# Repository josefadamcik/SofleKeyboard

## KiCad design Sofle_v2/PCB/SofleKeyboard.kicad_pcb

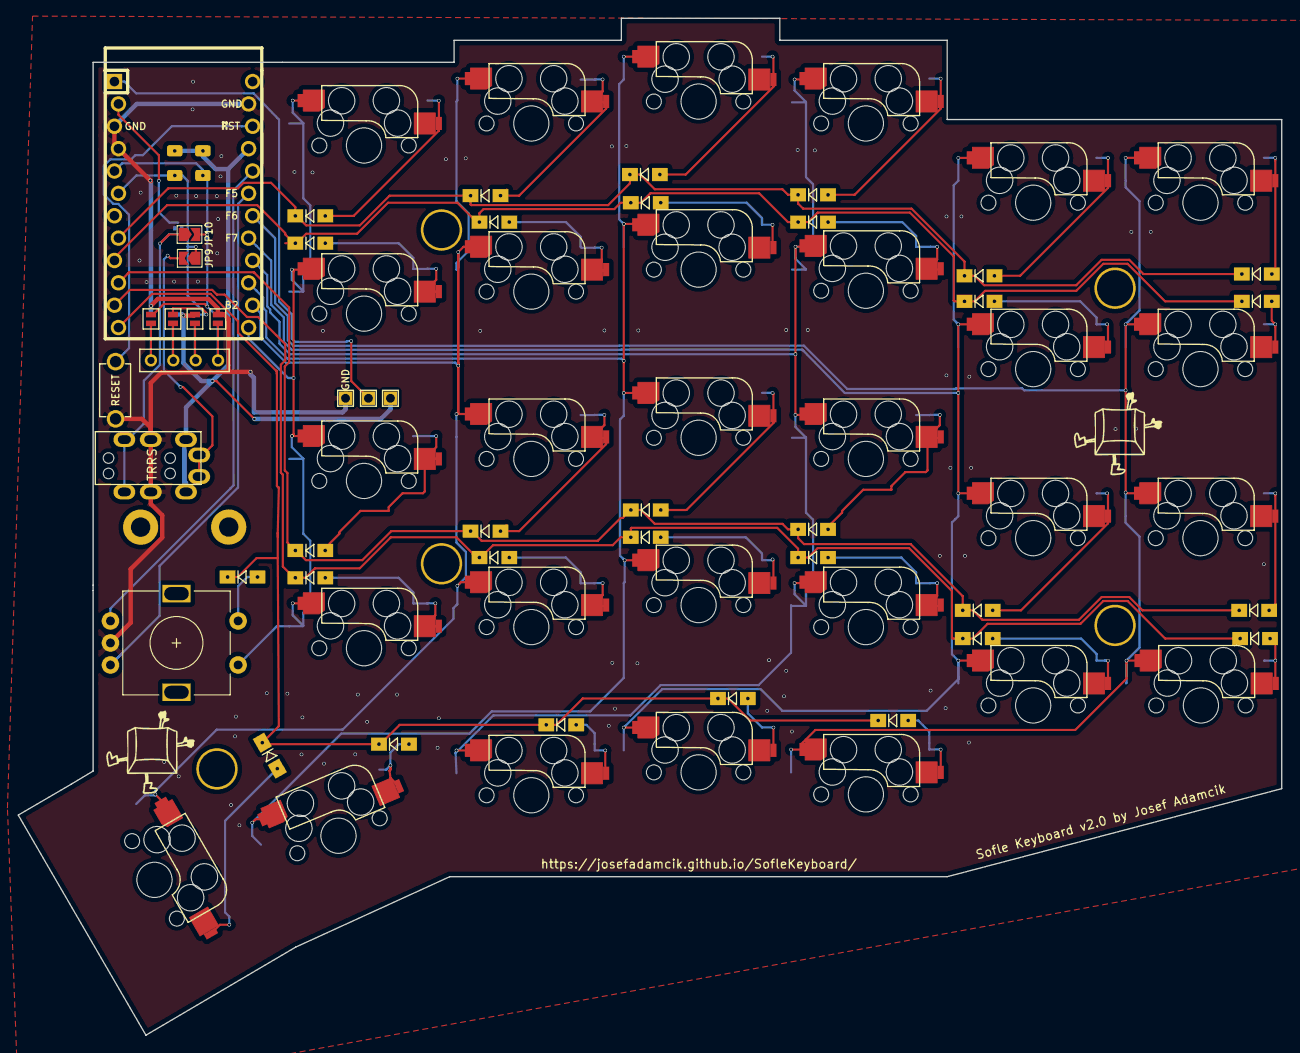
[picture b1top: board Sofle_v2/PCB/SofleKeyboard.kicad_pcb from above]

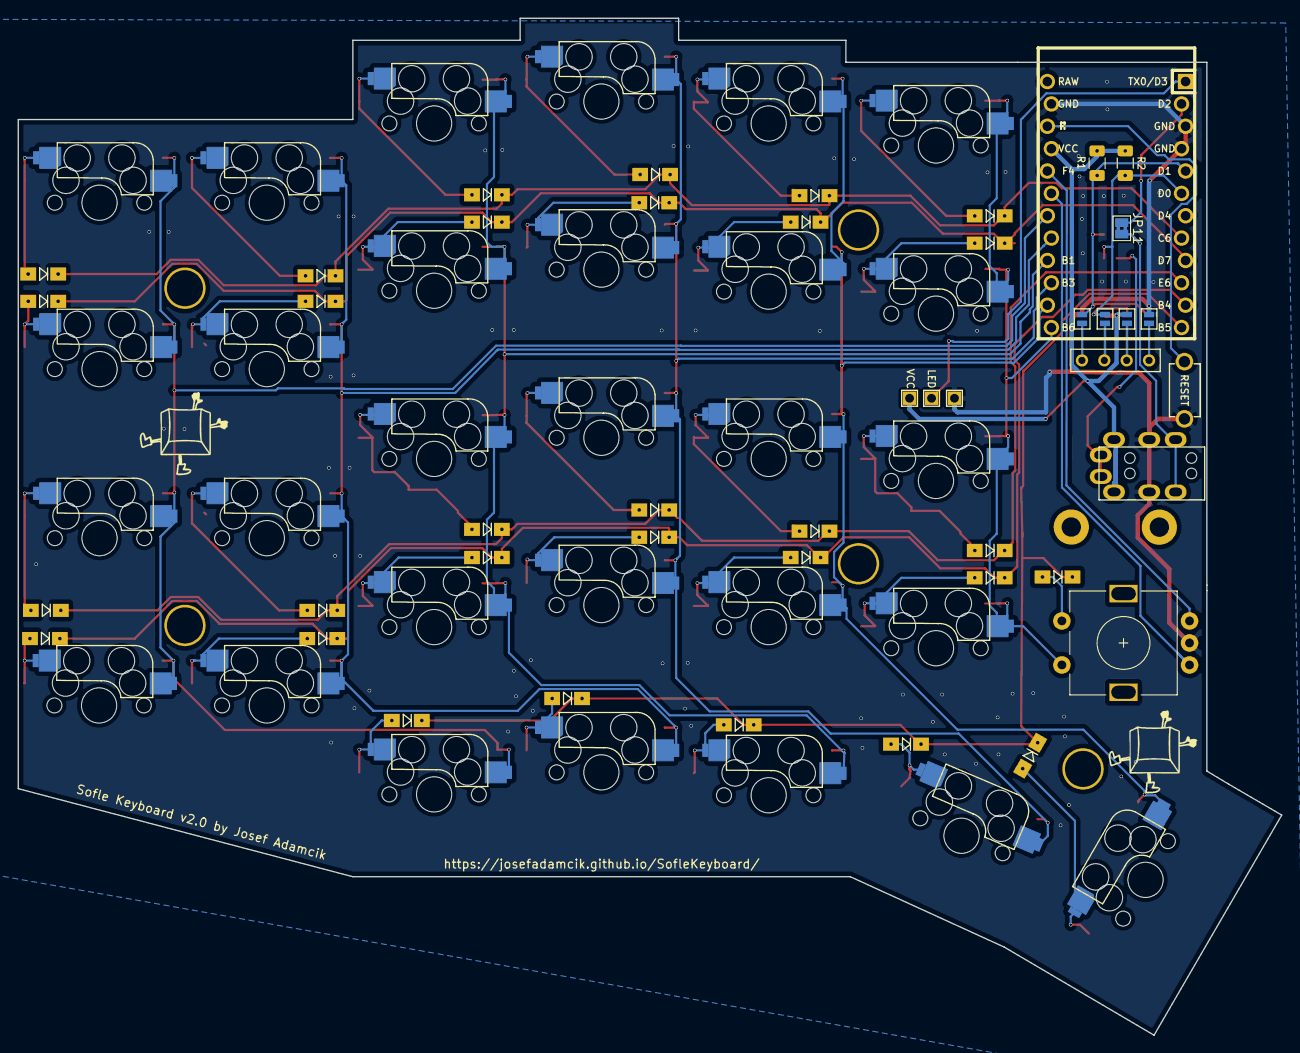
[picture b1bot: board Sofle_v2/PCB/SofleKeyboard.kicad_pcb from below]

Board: 2 copper layers, 143.5 x 115.5 mm, 89 parts (9 on the bottom side), 56 nets.

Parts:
D1, D2, D3, D4, D5, D6, D7, D8, D9, D10, D11, D12, D13, D14, D15, D16, D17, D18, D19, D20, D21, D22, D23, D24, D25, D26, D27, D28, D29, D30: D; Diode_SOD123
J1: LED
J2: 4PIN; MJ-4PP-9
J3: OLED; OLED_4Pin
JP1, JP2, JP3, JP4, JP5, JP6, JP7, JP8: Jumper_NO_Small; Jumper
JP9: I2CSCL; SolderJumper-2_P1.3mm_Open_TrianglePad1.0x1.5mm
JP10: IC2SDA; SolderJumper-2_P1.3mm_Open_TrianglePad1.0x1.5mm
JP11: Serial; SolderJumper-2_P1.3mm_Bridged2Bar_Pad1.0x1.5mm
R1, R2: R; R_1206_DoubleSided
RSW1: SW_RST; TACT_SWITCH_TVBP06
Ref**: Val**; SofleLogoSmall
Ref**#2, Ref**#3, Ref**#4: Val**; SofleLogoSmall
SW1, SW2, SW3, SW4, SW5, SW6, SW7, SW8, SW9, SW10, SW11, SW12, SW13, SW14, SW15, SW16, SW17, SW18, SW19, SW20, SW21, SW22, SW23, SW24, SW27, SW28, SW29, SW30: SW_PUSH; CherryMX_Hotswap
SW25: Rotary_Encoder_Switch; RotaryEncoder_Alps_EC11E-Switch_Vertical_H20mm-keebio_modif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
SW26: SW_PUSH; CherryMX_Hotswap_1.5
TH1, TH2: HOLE; M2_HOLE_PCB
TH3, TH4, TH5, TH6, TH7: HOLE; HOLE_M2_TH
U1: ProMicro; ArduinoProMicro-ZigZag-DoubleSided

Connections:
/i2c_c: J2.4, JP9.2
/i2c_d: J2.3, JP10.1, JP11.2
DATA: JP11.1, U1.2
ENCA: SW25.A, U1.20
ENCB: SW25.B, U1.19
GND: J1.3, J2.2, JP1.2, JP8.2, RSW1.1, SW25.C, U1.3, U1.4, U1.23
LED: J1.2, U1.1
unnamed: D1.2, SW1.2
unnamed: D2.2, SW2.2
unnamed: D3.2, SW3.2
unnamed: D4.2, SW4.2
unnamed: D5.2, SW5.2
unnamed: D6.2, SW6.2
unnamed: D7.2, SW7.2
unnamed: D8.2, SW8.2
unnamed: D9.2, SW9.2
unnamed: D10.2, SW10.2
unnamed: D11.2, SW11.2
unnamed: D12.2, SW12.2
unnamed: D13.2, SW13.2
unnamed: D14.2, SW14.2
unnamed: D15.2, SW15.2
unnamed: D16.2, SW16.2
unnamed: D17.2, SW17.2
unnamed: D18.2, SW18.2
unnamed: D19.2, SW19.2
unnamed: D20.2, SW20.2
unnamed: D21.2, SW21.2
unnamed: D22.2, SW22.2
unnamed: D23.2, SW23.2
unnamed: D24.2, SW24.2
unnamed: D26.2, SW26.2
unnamed: D27.2, SW27.2
unnamed: D28.2, SW28.2
unnamed: D29.2, SW29.2
unnamed: D30.2, SW30.2
unnamed: J3.1, JP4.1, JP8.1
unnamed: J3.2, JP3.1, JP7.1
unnamed: J3.3, JP2.1, JP6.1
unnamed: J3.4, JP1.1, JP5.1
RESET: RSW1.2, U1.22
SCL: JP3.2, JP6.2, JP9.1, R2.2, U1.6
SDA: JP4.2, JP5.2, JP10.2, R1.2, U1.5
SW25A: SW1.1, SW7.1, SW13.1, SW19.1, SW25.S1, U1.13
SW25B: D25.2, SW25.S2
VCC: J1.1, J2.1, JP2.2, JP7.2, R1.1, R2.1, U1.21
col0: SW6.1, SW12.1, SW18.1, SW24.1, SW30.1, U1.18
col1: SW5.1, SW11.1, SW17.1, SW23.1, SW29.1, U1.17
col2: SW4.1, SW10.1, SW16.1, SW22.1, SW28.1, U1.16
col3: SW3.1, SW9.1, SW15.1, SW21.1, SW27.1, U1.15
col4: SW2.1, SW8.1, SW14.1, SW20.1, SW26.1, U1.14
row0: D1.1, D2.1, D3.1, D4.1, D5.1, D6.1, U1.8
row1: D7.1, D8.1, D9.1, D10.1, D11.1, D12.1, U1.9
row2: D13.1, D14.1, D15.1, D16.1, D17.1, D18.1, U1.10
row3: D19.1, D20.1, D21.1, D22.1, D23.1, D24.1, U1.11
row4: D25.1, D26.1, D27.1, D28.1, D29.1, D30.1, U1.12

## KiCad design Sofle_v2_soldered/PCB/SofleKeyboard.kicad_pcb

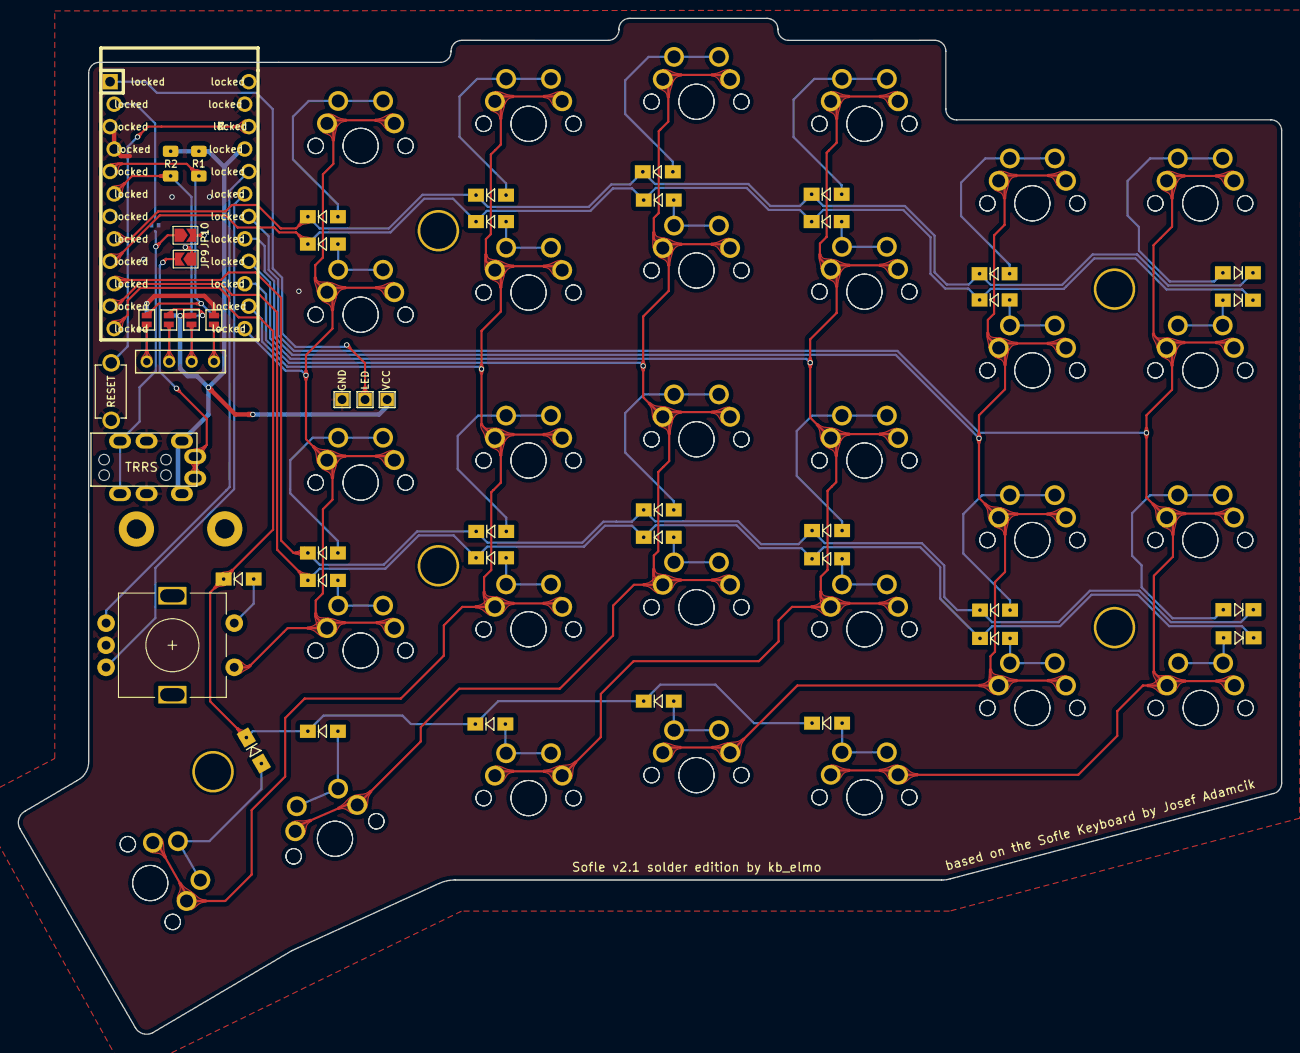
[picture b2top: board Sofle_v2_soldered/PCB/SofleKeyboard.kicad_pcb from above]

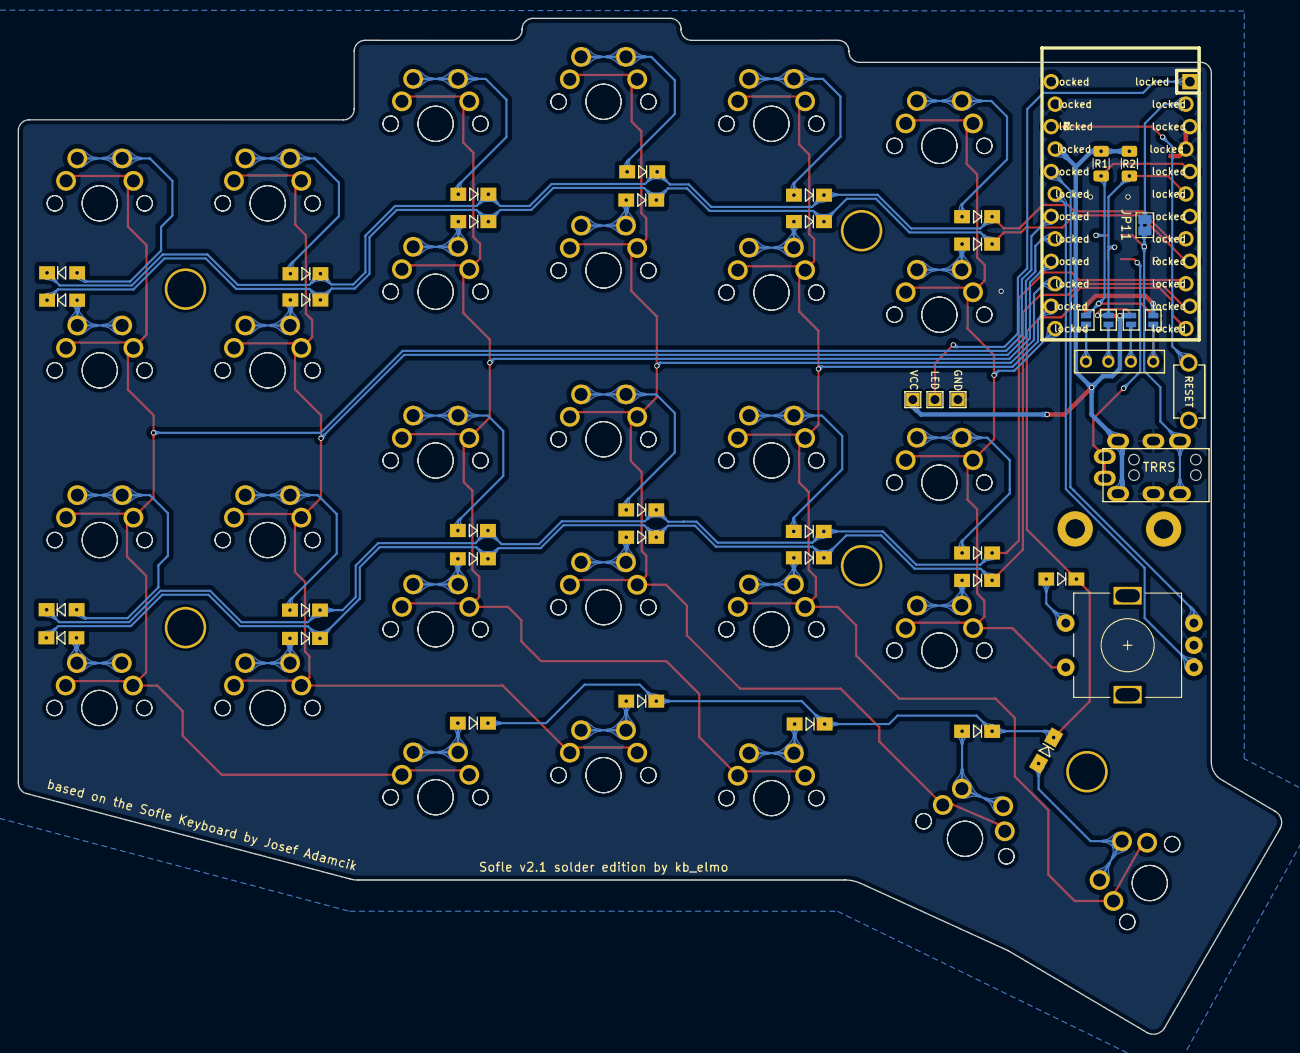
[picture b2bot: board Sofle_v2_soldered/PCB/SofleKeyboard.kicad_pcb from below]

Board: 2 copper layers, 142.9 x 114.9 mm, 114 parts (36 on the bottom side), 56 nets.

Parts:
D1, D2, D3, D4, D5, D6, D7, D8, D9, D10, D11, D12, D13, D14, D15, D16, D17, D18, D19, D20, D21, D22, D23, D24, D25, D26, D27, D28, D29, D30: D; Diode_SOD123
J1: LED
J2: 4PIN; MJ-4PP-9
J3: OLED; OLED_4Pin
JP1, JP2, JP3, JP4, JP5, JP6, JP7, JP8: Jumper_NO_Small; Jumper
JP9: I2CSCL; SolderJumper-2_P1.3mm_Open_TrianglePad1.0x1.5mm
JP10: IC2SDA; SolderJumper-2_P1.3mm_Open_TrianglePad1.0x1.5mm
JP11: Serial; SolderJumper-2_P1.3mm_Bridged2Bar_Pad1.0x1.5mm
R1, R2: R; R_1206_DoubleSided
RSW1: SW_RST; TACT_SWITCH_TVBP06
SW1, SW1#2, SW2, SW2#2, SW3, SW3#2, SW4, SW4#2, SW5, SW5#2, SW6, SW6#2, SW7, SW7#2, SW8, SW8#2, SW9, SW9#2, SW10, SW10#2, SW11, SW11#2, SW12, SW12#2, SW13, SW13#2, SW14, SW14#2, SW15, SW15#2, SW16, SW16#2, SW17, SW17#2, SW18, SW18#2, SW19, SW19#2, SW20, SW20#2, SW21, SW21#2, SW22, SW22#2, SW23, SW23#2, SW24, SW24#2, SW27, SW27#2, SW28, SW28#2, SW29, SW29#2, SW30, SW30#2: SW_PUSH; MXOnly-1U-NoLED
SW25: Rotary_Encoder_Switch; RotaryEncoder_Alps_EC11E-Switch_Vertical_H20mm-keebio_modif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
SW26, SW26#2: SW_PUSH; MXOnly-1.5U-NoLED
TH1, TH2: HOLE; M2_HOLE_PCB
TH3, TH4, TH5, TH6, TH7: HOLE; HOLE_M2_TH
locked: locked; ArduinoProMicro-ZigZag-DoubleSided

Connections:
/i2c_c: J2.4, JP9.2
/i2c_d: J2.3, JP10.1, JP11.2
DATA: JP11.1, locked.2 (RX(PD2))
ENCA: SW25.A, locked.20 (A3(PF4))
ENCB: SW25.B, locked.19 (A2(PF5))
GND: J1.3, J2.2, JP1.2, JP8.2, RSW1.1, SW25.C, locked.3 (GND), locked.4 (GND), locked.23 (GND)
LED: J1.2, locked.1 (TX(PD3))
unnamed: D1.2 (A), SW1.2, SW1#2.2
unnamed: D2.2 (A), SW2.2, SW2#2.2
unnamed: D3.2 (A), SW3.2, SW3#2.2
unnamed: D4.2 (A), SW4.2, SW4#2.2
unnamed: D5.2 (A), SW5.2, SW5#2.2
unnamed: D6.2 (A), SW6.2, SW6#2.2
unnamed: D7.2 (A), SW7.2, SW7#2.2
unnamed: D8.2 (A), SW8.2, SW8#2.2
unnamed: D9.2 (A), SW9.2, SW9#2.2
unnamed: D10.2 (A), SW10.2, SW10#2.2
unnamed: D11.2 (A), SW11.2, SW11#2.2
unnamed: D12.2 (A), SW12.2, SW12#2.2
unnamed: D13.2 (A), SW13.2, SW13#2.2
unnamed: D14.2 (A), SW14.2, SW14#2.2
unnamed: D15.2 (A), SW15.2, SW15#2.2
unnamed: D16.2 (A), SW16.2, SW16#2.2
unnamed: D17.2 (A), SW17.2, SW17#2.2
unnamed: D18.2 (A), SW18.2, SW18#2.2
unnamed: D19.2 (A), SW19.2, SW19#2.2
unnamed: D20.2 (A), SW20.2, SW20#2.2
unnamed: D21.2 (A), SW21.2, SW21#2.2
unnamed: D22.2 (A), SW22.2, SW22#2.2
unnamed: D23.2 (A), SW23.2, SW23#2.2
unnamed: D24.2 (A), SW24.2, SW24#2.2
unnamed: D26.2 (A), SW26.2, SW26#2.2
unnamed: D27.2 (A), SW27.2, SW27#2.2
unnamed: D28.2 (A), SW28.2, SW28#2.2
unnamed: D29.2 (A), SW29.2, SW29#2.2
unnamed: D30.2 (A), SW30.2, SW30#2.2
unnamed: J3.1, JP4.1, JP8.1
unnamed: J3.2, JP3.1, JP7.1
unnamed: J3.3, JP2.1, JP6.1
unnamed: J3.4, JP1.1, JP5.1
RESET: RSW1.2, locked.22 (RST)
SCL: JP3.2, JP6.2, JP9.1, R2.2, locked.6 (SCL(PD0))
SDA: JP4.2, JP5.2, JP10.2, R1.2, locked.5 (SDA(PD1))
SW25A: SW1.1, SW1#2.1, SW7.1, SW7#2.1, SW13.1, SW13#2.1, SW19.1, SW19#2.1, SW25.S1, locked.13 (D10(PB6))
SW25B: D25.2 (A), SW25.S2
VCC: J1.1, J2.1, JP2.2, JP7.2, R1.1, R2.1, locked.21 (VCC)
col0: SW6.1, SW6#2.1, SW12.1, SW12#2.1, SW18.1, SW18#2.1, SW24.1, SW24#2.1, SW30.1, SW30#2.1, locked.18 (A1(PF6))
col1: SW5.1, SW5#2.1, SW11.1, SW11#2.1, SW17.1, SW17#2.1, SW23.1, SW23#2.1, SW29.1, SW29#2.1, locked.17 (A0(PF7))
col2: SW4.1, SW4#2.1, SW10.1, SW10#2.1, SW16.1, SW16#2.1, SW22.1, SW22#2.1, SW28.1, SW28#2.1, locked.16 (D15(PB1))
col3: SW3.1, SW3#2.1, SW9.1, SW9#2.1, SW15.1, SW15#2.1, SW21.1, SW21#2.1, SW27.1, SW27#2.1, locked.15 (D14(PB3))
col4: SW2.1, SW2#2.1, SW8.1, SW8#2.1, SW14.1, SW14#2.1, SW20.1, SW20#2.1, SW26.1, SW26#2.1, locked.14 (D16(PB2))
row0: D1.1 (K), D2.1 (K), D3.1 (K), D4.1 (K), D5.1 (K), D6.1 (K), locked.8 (D5(PC6))
row1: D7.1 (K), D8.1 (K), D9.1 (K), D10.1 (K), D11.1 (K), D12.1 (K), locked.9 (D6(PD7))
row2: D13.1 (K), D14.1 (K), D15.1 (K), D16.1 (K), D17.1 (K), D18.1 (K), locked.10 (D7(PE6))
row3: D19.1 (K), D20.1 (K), D21.1 (K), D22.1 (K), D23.1 (K), D24.1 (K), locked.11 (D8(PB4))
row4: D25.1 (K), D26.1 (K), D27.1 (K), D28.1 (K), D29.1 (K), D30.1 (K), locked.12 (D9(PB5))
